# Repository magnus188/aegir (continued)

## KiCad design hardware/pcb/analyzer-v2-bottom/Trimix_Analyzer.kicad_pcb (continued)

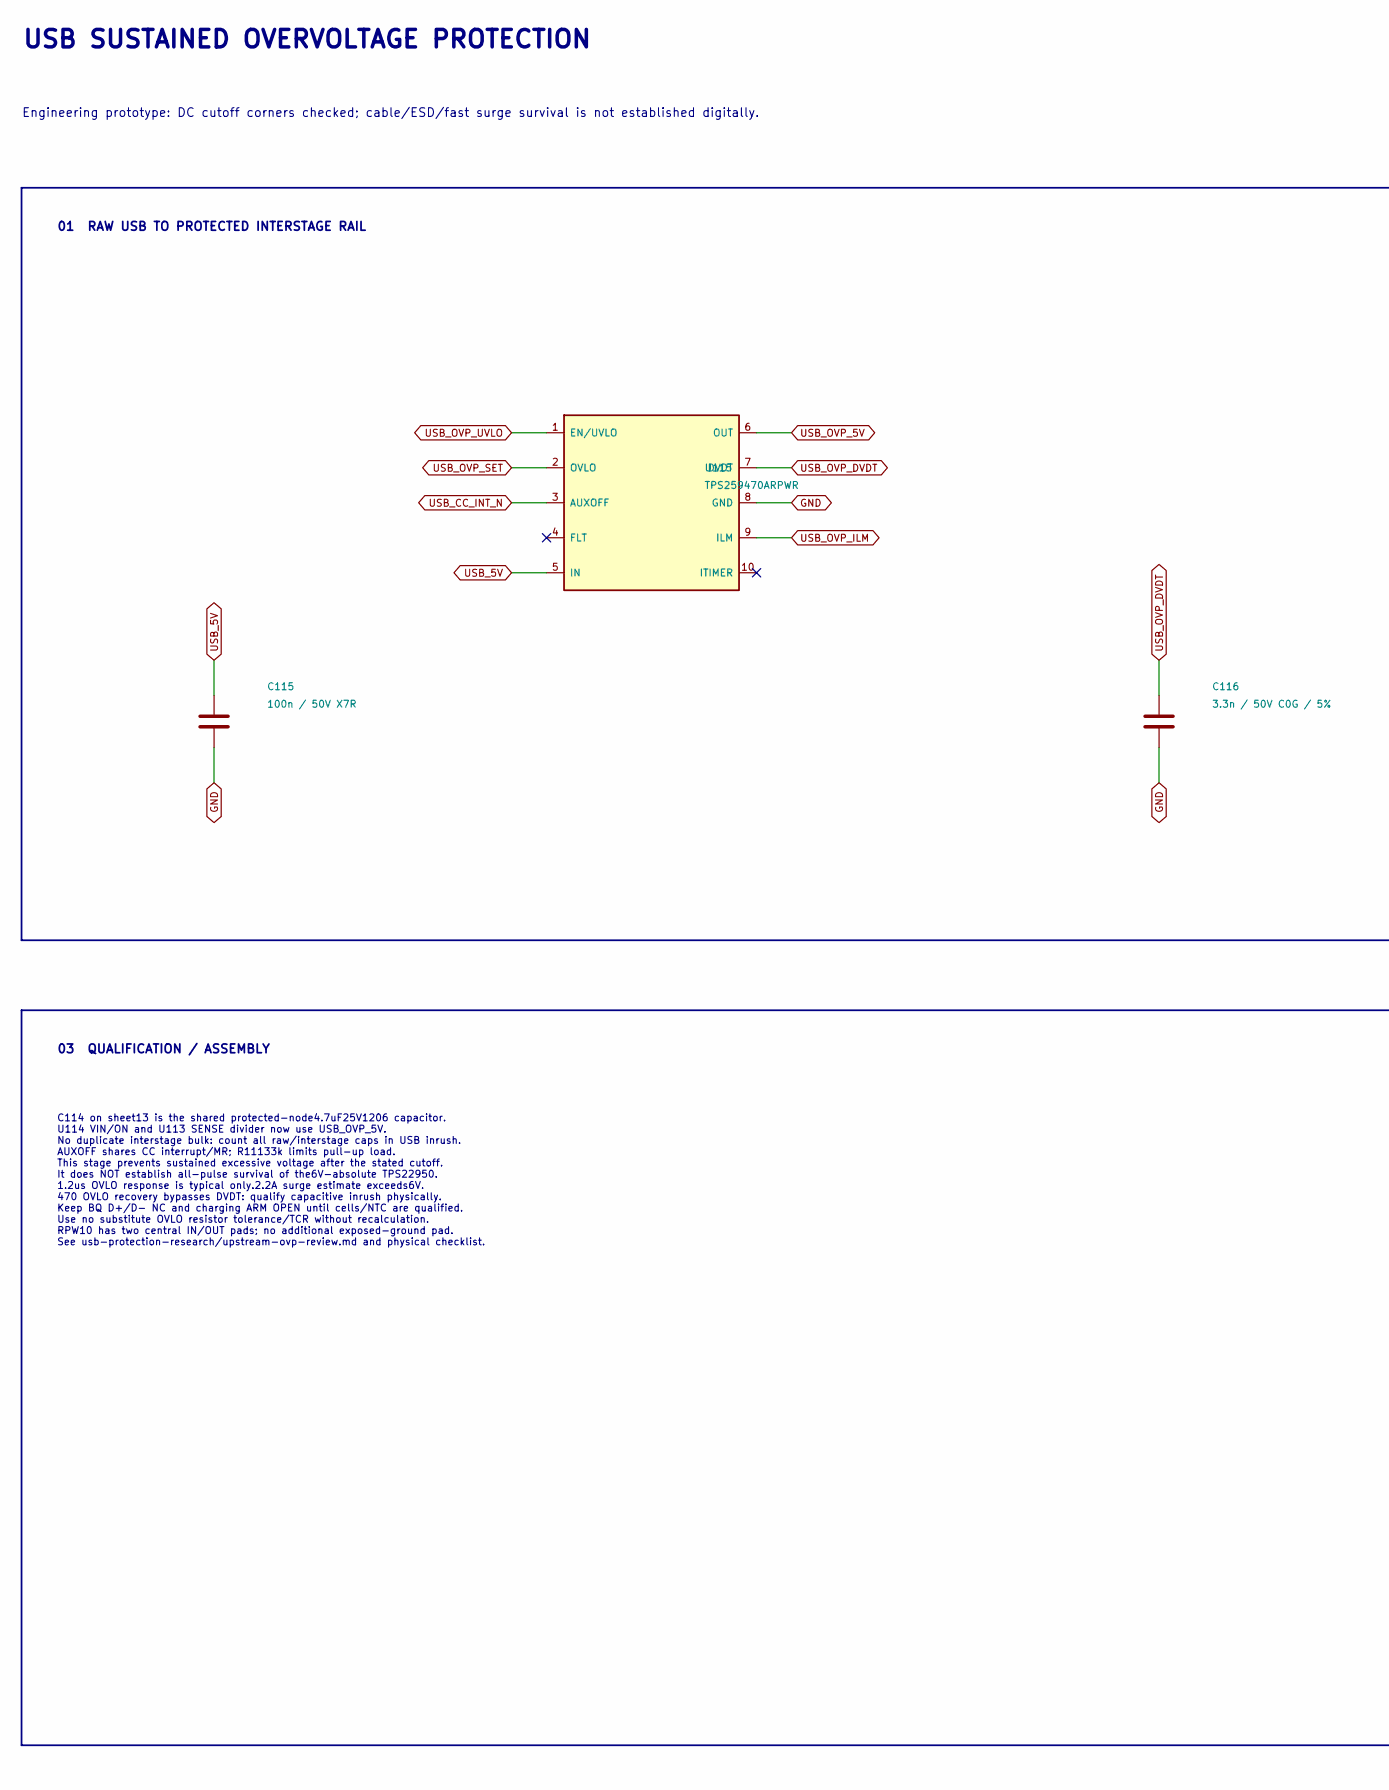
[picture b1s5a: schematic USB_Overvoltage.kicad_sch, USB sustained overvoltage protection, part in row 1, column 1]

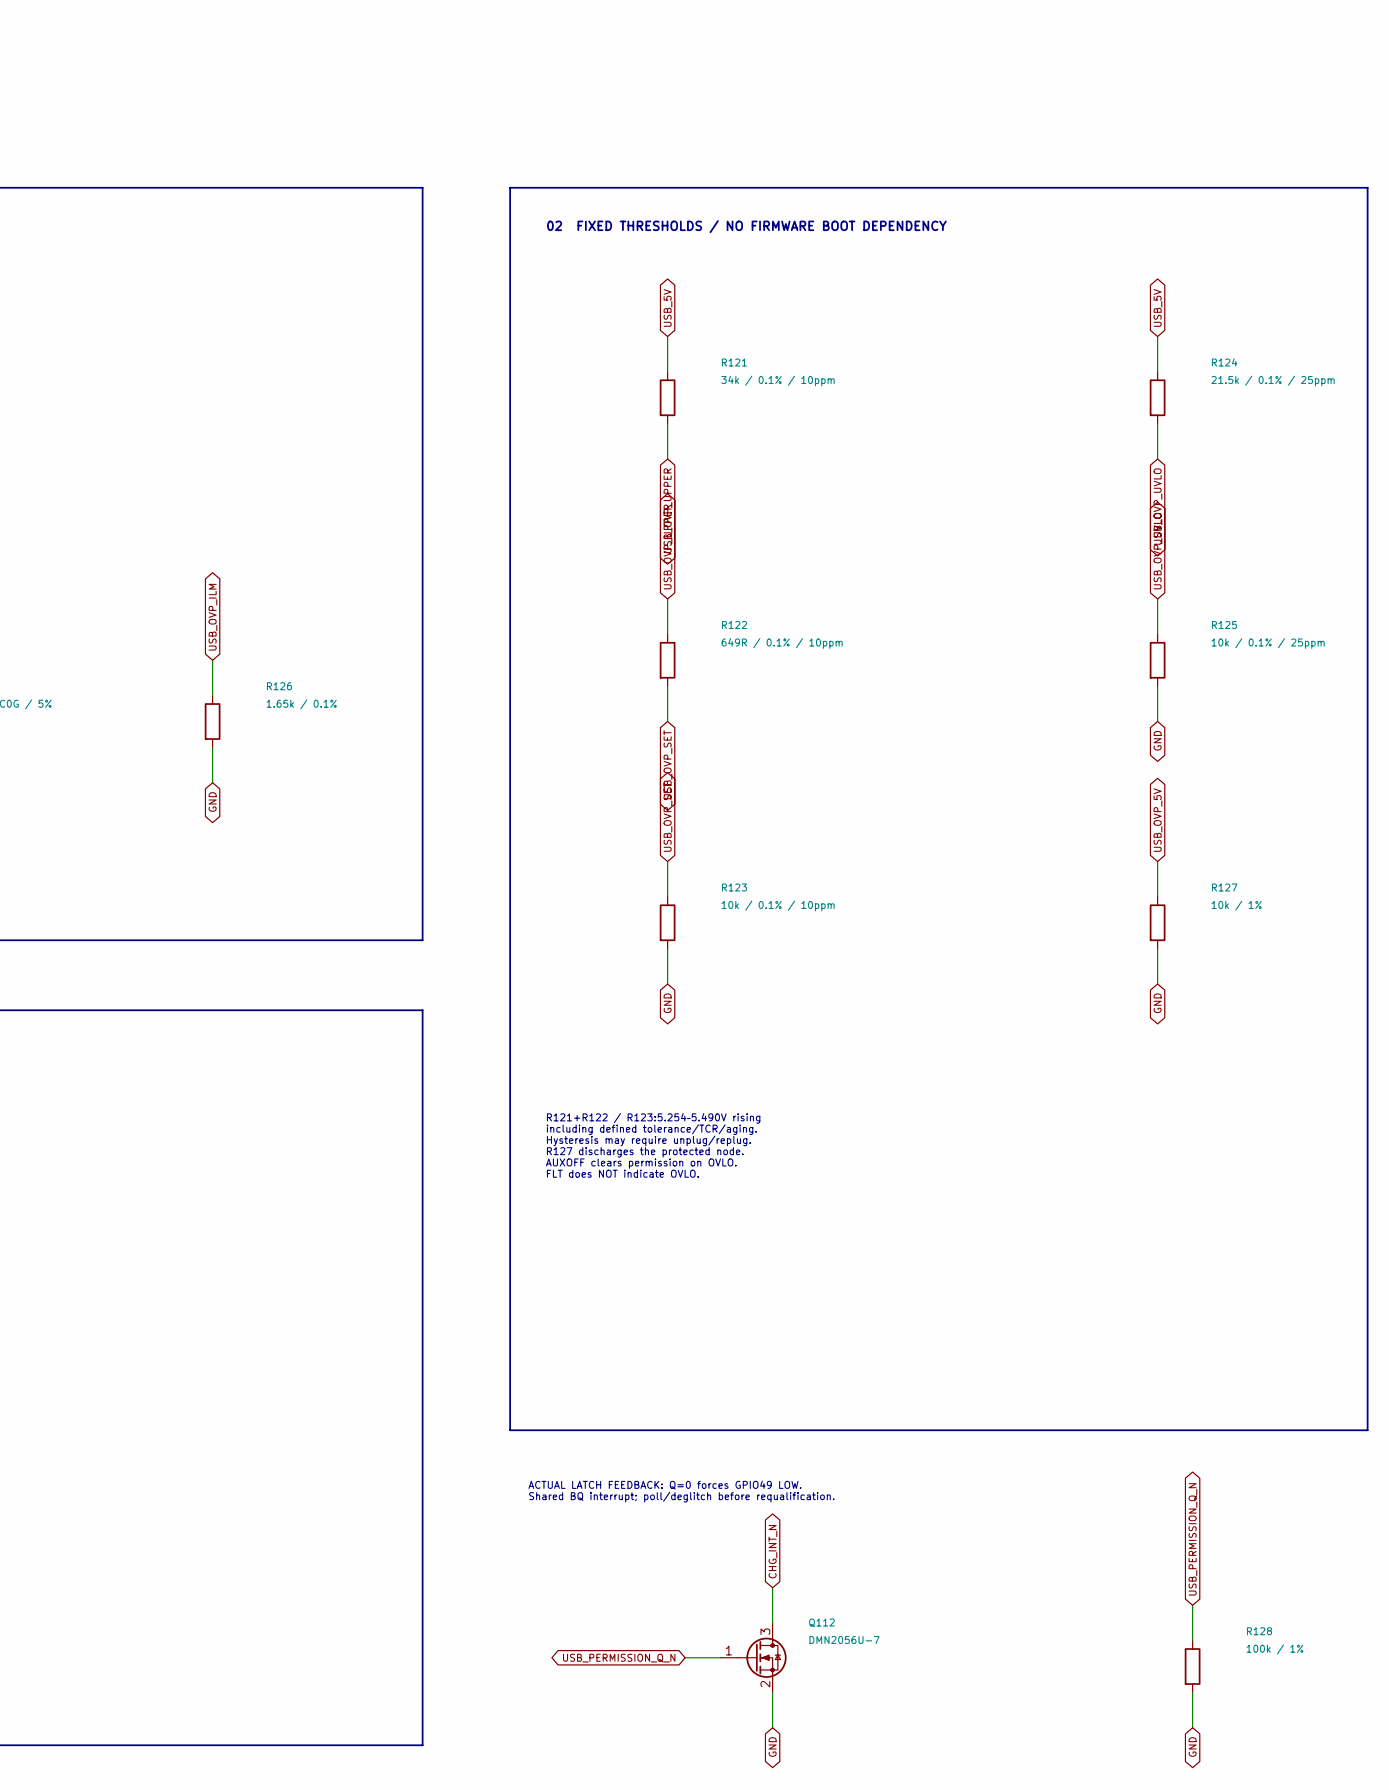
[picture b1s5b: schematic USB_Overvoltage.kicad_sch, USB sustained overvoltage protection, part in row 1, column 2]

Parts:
C115: 100n / 50V X7R; C_0603_1608Metric; MPN C1608X7R1H104K080AA
C116: 3.3n / 50V C0G / 5%; C_0402_1005Metric; MPN GRM1555C1H332JE01D
Q112: DMN2056U-7; SOT-23; MPN DMN2056U-7
R121: 34k / 0.1% / 10ppm; R_0603_1608Metric; MPN TNPW060334K0BYEA
R122: 649R / 0.1% / 10ppm; R_0603_1608Metric; MPN TNPW0603649RBYEA
R123: 10k / 0.1% / 10ppm; R_0603_1608Metric; MPN TNPW060310K0BYEA
R124: 21.5k / 0.1% / 25ppm; R_0603_1608Metric; MPN TNPW060321K5BEEA
R125: 10k / 0.1% / 25ppm; R_0603_1608Metric; MPN TNPW060310K0BEEA
R126: 1.65k / 0.1%; R_0603_1608Metric; MPN TNPW06031K65BEEA
R127: 10k / 1%; R_0603_1608Metric; MPN RC0603FR-0710KL
R128: 100k / 1%; R_0603_1608Metric; MPN RC0603FR-07100KL
U115: TPS259470ARPWR; TI_RPW0010A; MPN TPS259470ARPWR

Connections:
CHG_INT_N: Q112.3 (D); also elsewhere on the board
GND: C115.2, C116.2, Q112.2 (S), R123.2, R125.2, R126.2, R127.2, R128.2, U115.8 (GND); also elsewhere on the board
USB_5V: C115.1, R121.1, R124.1, U115.5 (IN); also elsewhere on the board
USB_CC_INT_N: U115.3 (AUXOFF); also elsewhere on the board
USB_OVP_5V: R127.1, U115.6 (OUT); also elsewhere on the board
USB_OVP_DVDT: C116.1, U115.7 (DVDT)
USB_OVP_ILM: R126.1, U115.9 (ILM)
USB_OVP_SET: R122.2, R123.1, U115.2 (OVLO)
USB_OVP_UPPER: R121.2, R122.1
USB_OVP_UVLO: R124.2, R125.1, U115.1 (EN/UVLO)
USB_PERMISSION_Q_N: Q112.1 (G), R128.1; also elsewhere on the board

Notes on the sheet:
C114 on sheet13 is the shared protected-node4.7uF25V1206 capacitor. U114 VIN/ON and U113 SENSE divider now use USB_OVP_5V. No duplicate interstage bulk: count all raw/interstage caps in USB inrush. AUXOFF shares CC interrupt/MR; R11133k limits pull-up load. This stage prevents sustained excessive v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
01 RAW USB TO PROTECTED INTERSTAGE RAIL
USB SUSTAINED OVERVOLTAGE PROTECTION
Engineering prototype: DC cutoff corners checked; cable/ESD/fast surge survival is not established digitally.
03 QUALIFICATION / ASSEMBLY
R121+R122 / R123:5.254–5.490V rising including defined tolerance/TCR/aging. Hysteresis may require unplug/replug. R127 discharges the protected node. AUXOFF clears permission on OVLO. FLT does NOT indicate OVLO.
02 FIXED THRESHOLDS / NO FIRMWARE BOOT DEPENDENCY
ACTUAL LATCH FEEDBACK: Q=0 forces GPIO49 LOW. Shared BQ interrupt; poll/deglitch before requalification.

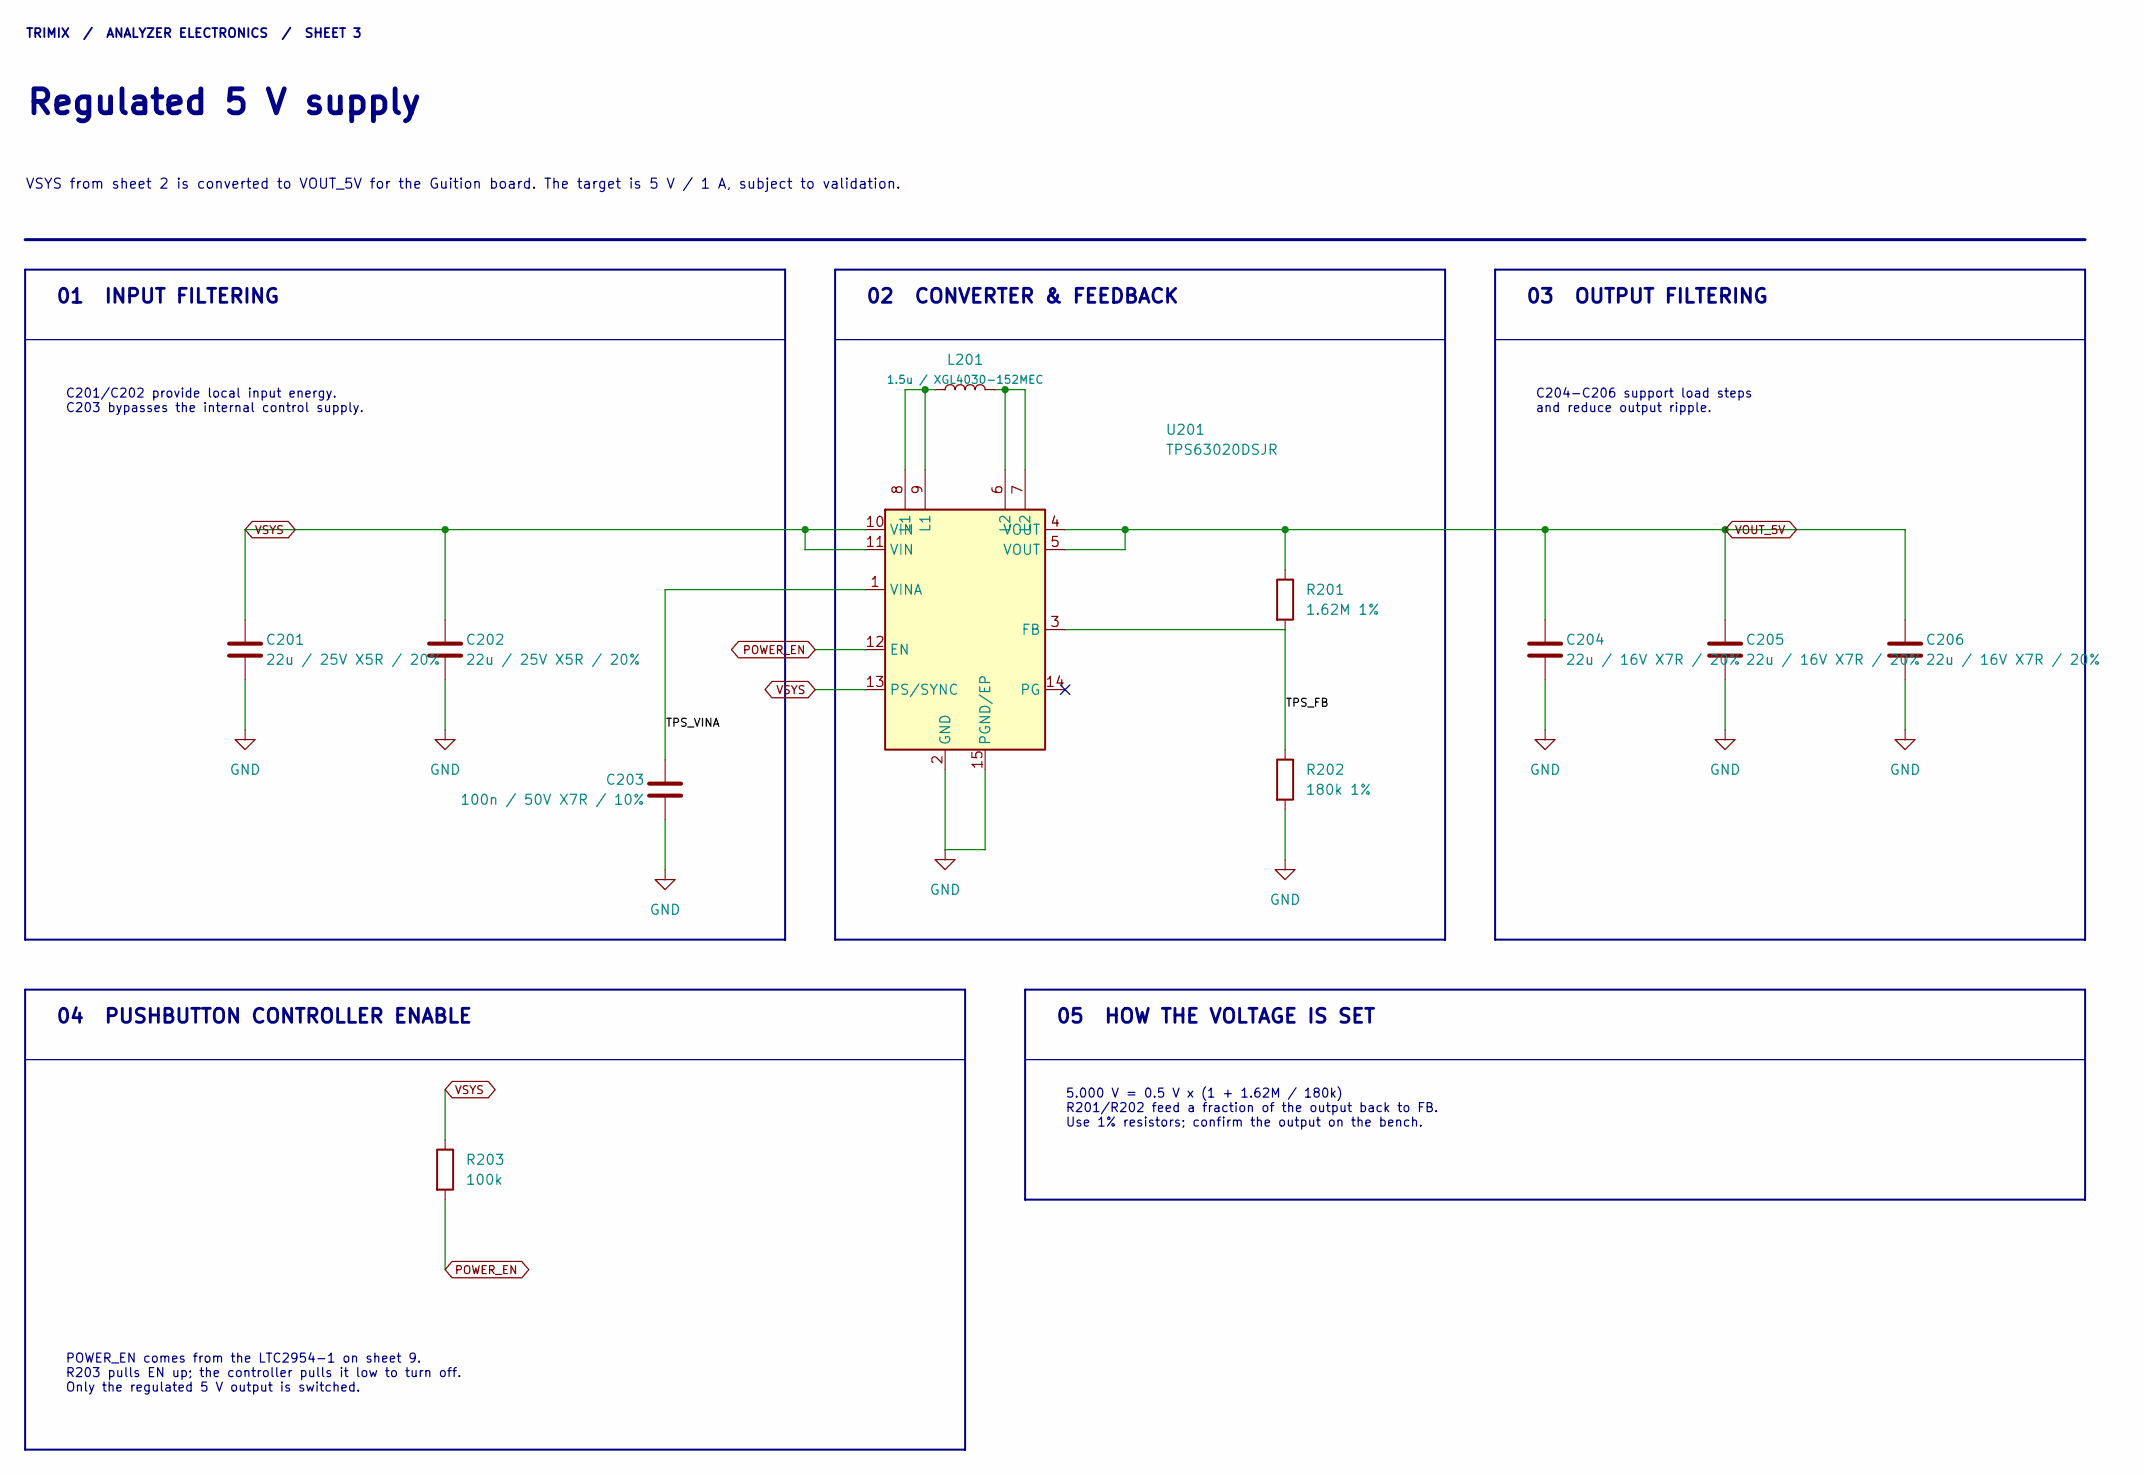
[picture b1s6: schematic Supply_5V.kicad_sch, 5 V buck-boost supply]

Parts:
C201, C202: 22u / 25V X5R / 20%; C_1206_3216Metric; MPN C3216X5R1E226M160AB
C203: 100n / 50V X7R / 10%; C_0603_1608Metric; MPN C1608X7R1H104K080AA
C204, C205, C206: 22u / 16V X7R / 20%; C_1210_3225Metric; MPN C3225X7R1C226M250AC
L201: 1.5u / XGL4030-152MEC; L_Coilcraft_XGL4030; MPN XGL4030-152MEC
R201: 1.62M 1%; R_0603_1608Metric; MPN RC0603FR-071M62L
R202: 180k 1%; R_0603_1608Metric; MPN RC0603FR-07180KL
R203: 100k; R_0603_1608Metric; MPN RC0603FR-07100KL
U201: TPS63020DSJR; TI_DSJ_14; MPN TPS63020DSJR

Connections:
/02 SWITCHED 5 V/TPS_FB: R201.2, R202.1, U201.3 (FB)
/02 SWITCHED 5 V/TPS_VINA: C203.1, U201.1 (VINA)
GND: C201.2, C202.2, C203.2, C204.2, C205.2, C206.2, R202.2, U201.2 (GND), U201.15 (PGND/EP); also elsewhere on the board
unnamed: L201.1, U201.8 (L1), U201.9 (L1)
unnamed: L201.2, U201.6 (L2), U201.7 (L2)
POWER_EN: R203.2, U201.12 (EN); also elsewhere on the board
VOUT_5V: C204.1, C205.1, C206.1, R201.1, U201.4 (VOUT), U201.5 (VOUT); also elsewhere on the board
VSYS: C201.1, C202.1, R203.1, U201.10 (VIN), U201.11 (VIN), U201.13 (PS/SYNC); also elsewhere on the board

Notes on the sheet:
02 CONVERTER & FEEDBACK
C204-C206 support load steps and reduce output ripple.
5.000 V = 0.5 V x (1 + 1.62M / 180k) R201/R202 feed a fraction of the output back to FB. Use 1% resistors; confirm the output on the bench.
VSYS from sheet 2 is converted to VOUT_5V for the Guition board. The target is 5 V / 1 A, subject to validation.
TRIMIX / ANALYZER ELECTRONICS / SHEET 3
05 HOW THE VOLTAGE IS SET
01 INPUT FILTERING
04 PUSHBUTTON CONTROLLER ENABLE
Regulated 5 V supply
C201/C202 provide local input energy. C203 bypasses the internal control supply.
03 OUTPUT FILTERING
POWER_EN comes from the LTC2954-1 on sheet 9. R203 pulls EN up; the controller pulls it low to turn off. Only the regulated 5 V output is switched.

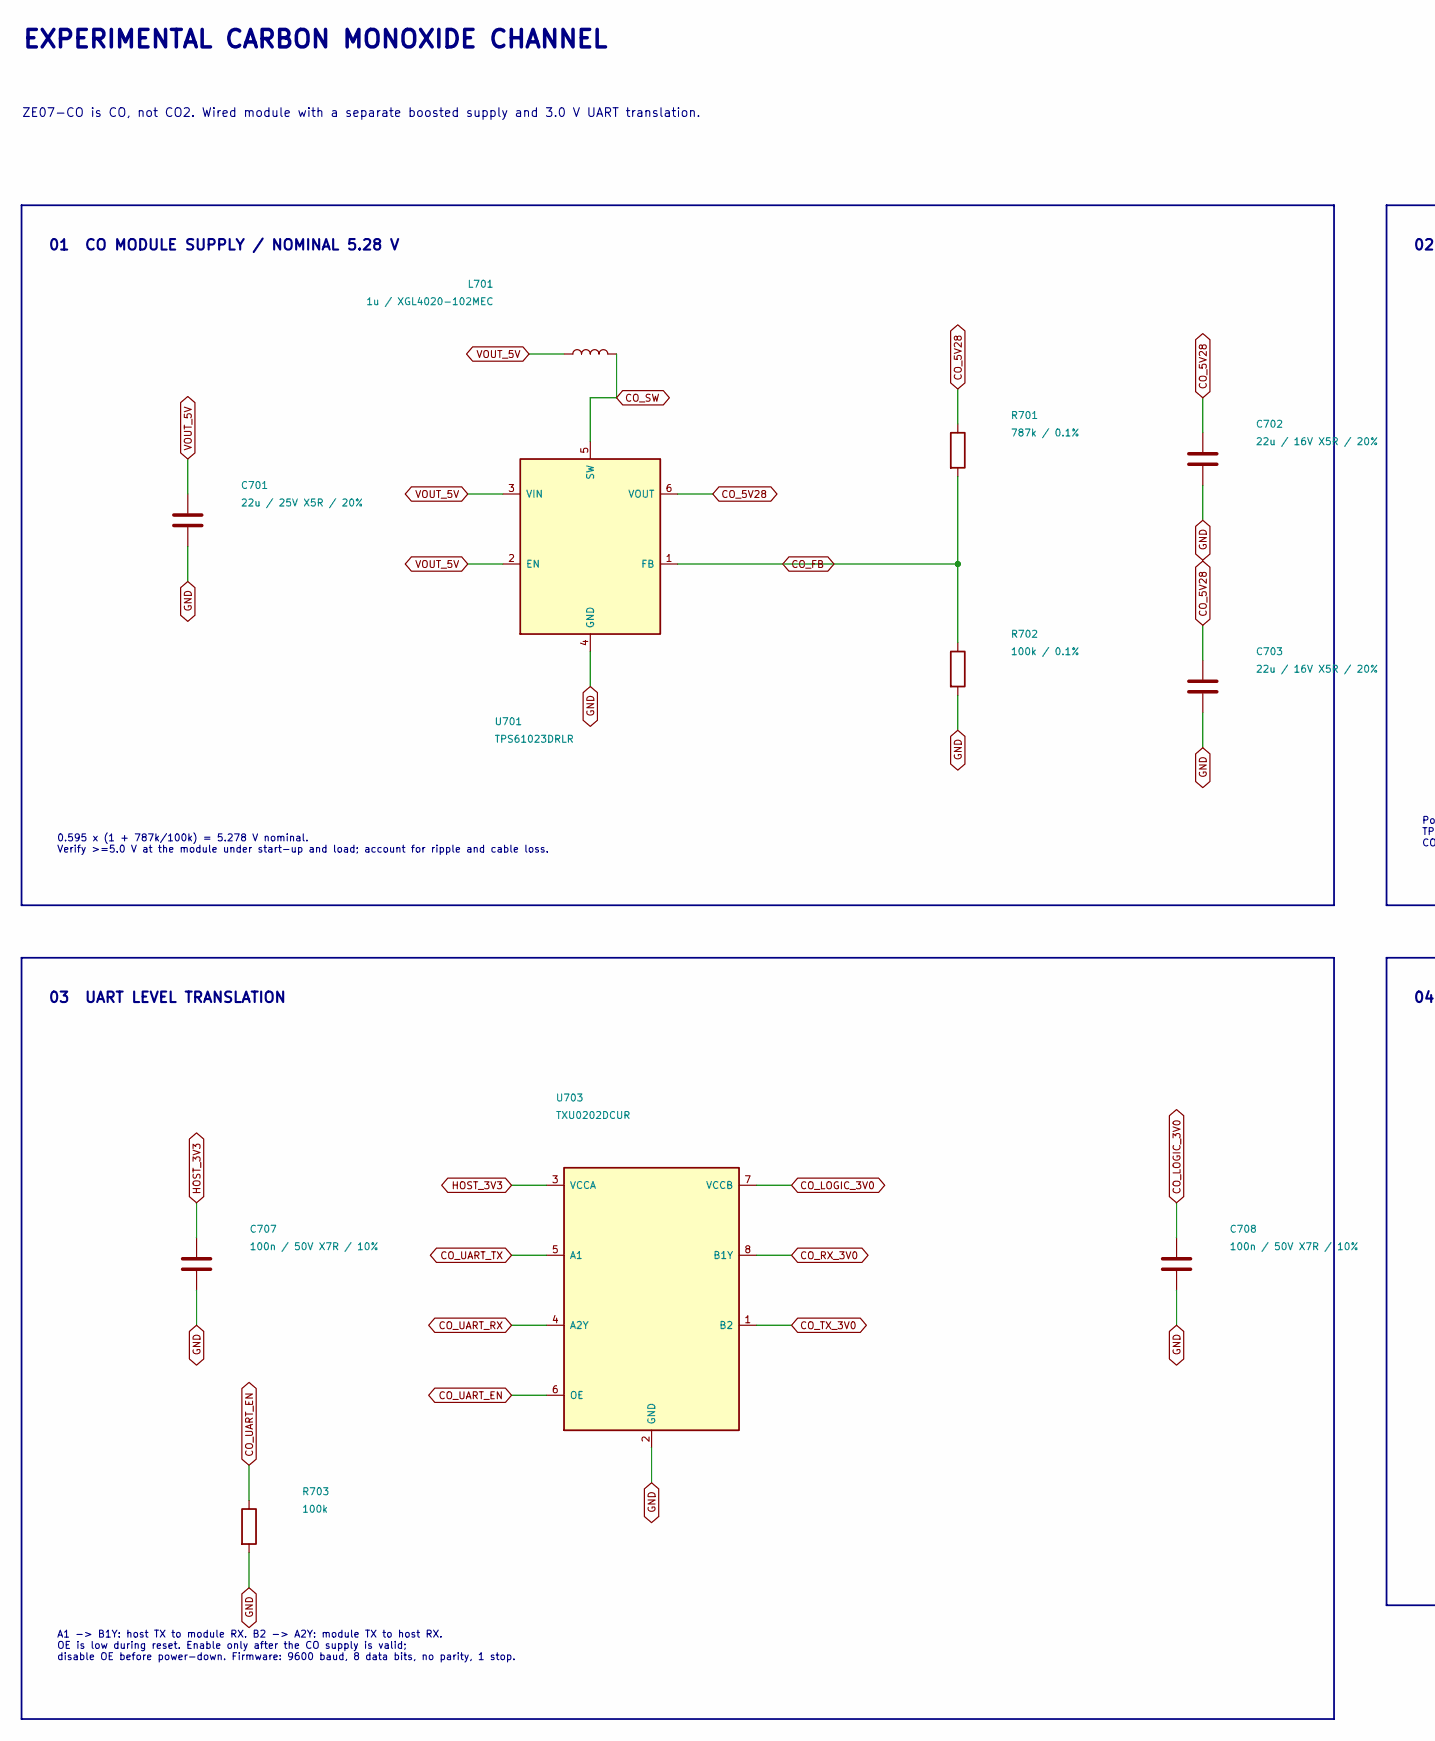
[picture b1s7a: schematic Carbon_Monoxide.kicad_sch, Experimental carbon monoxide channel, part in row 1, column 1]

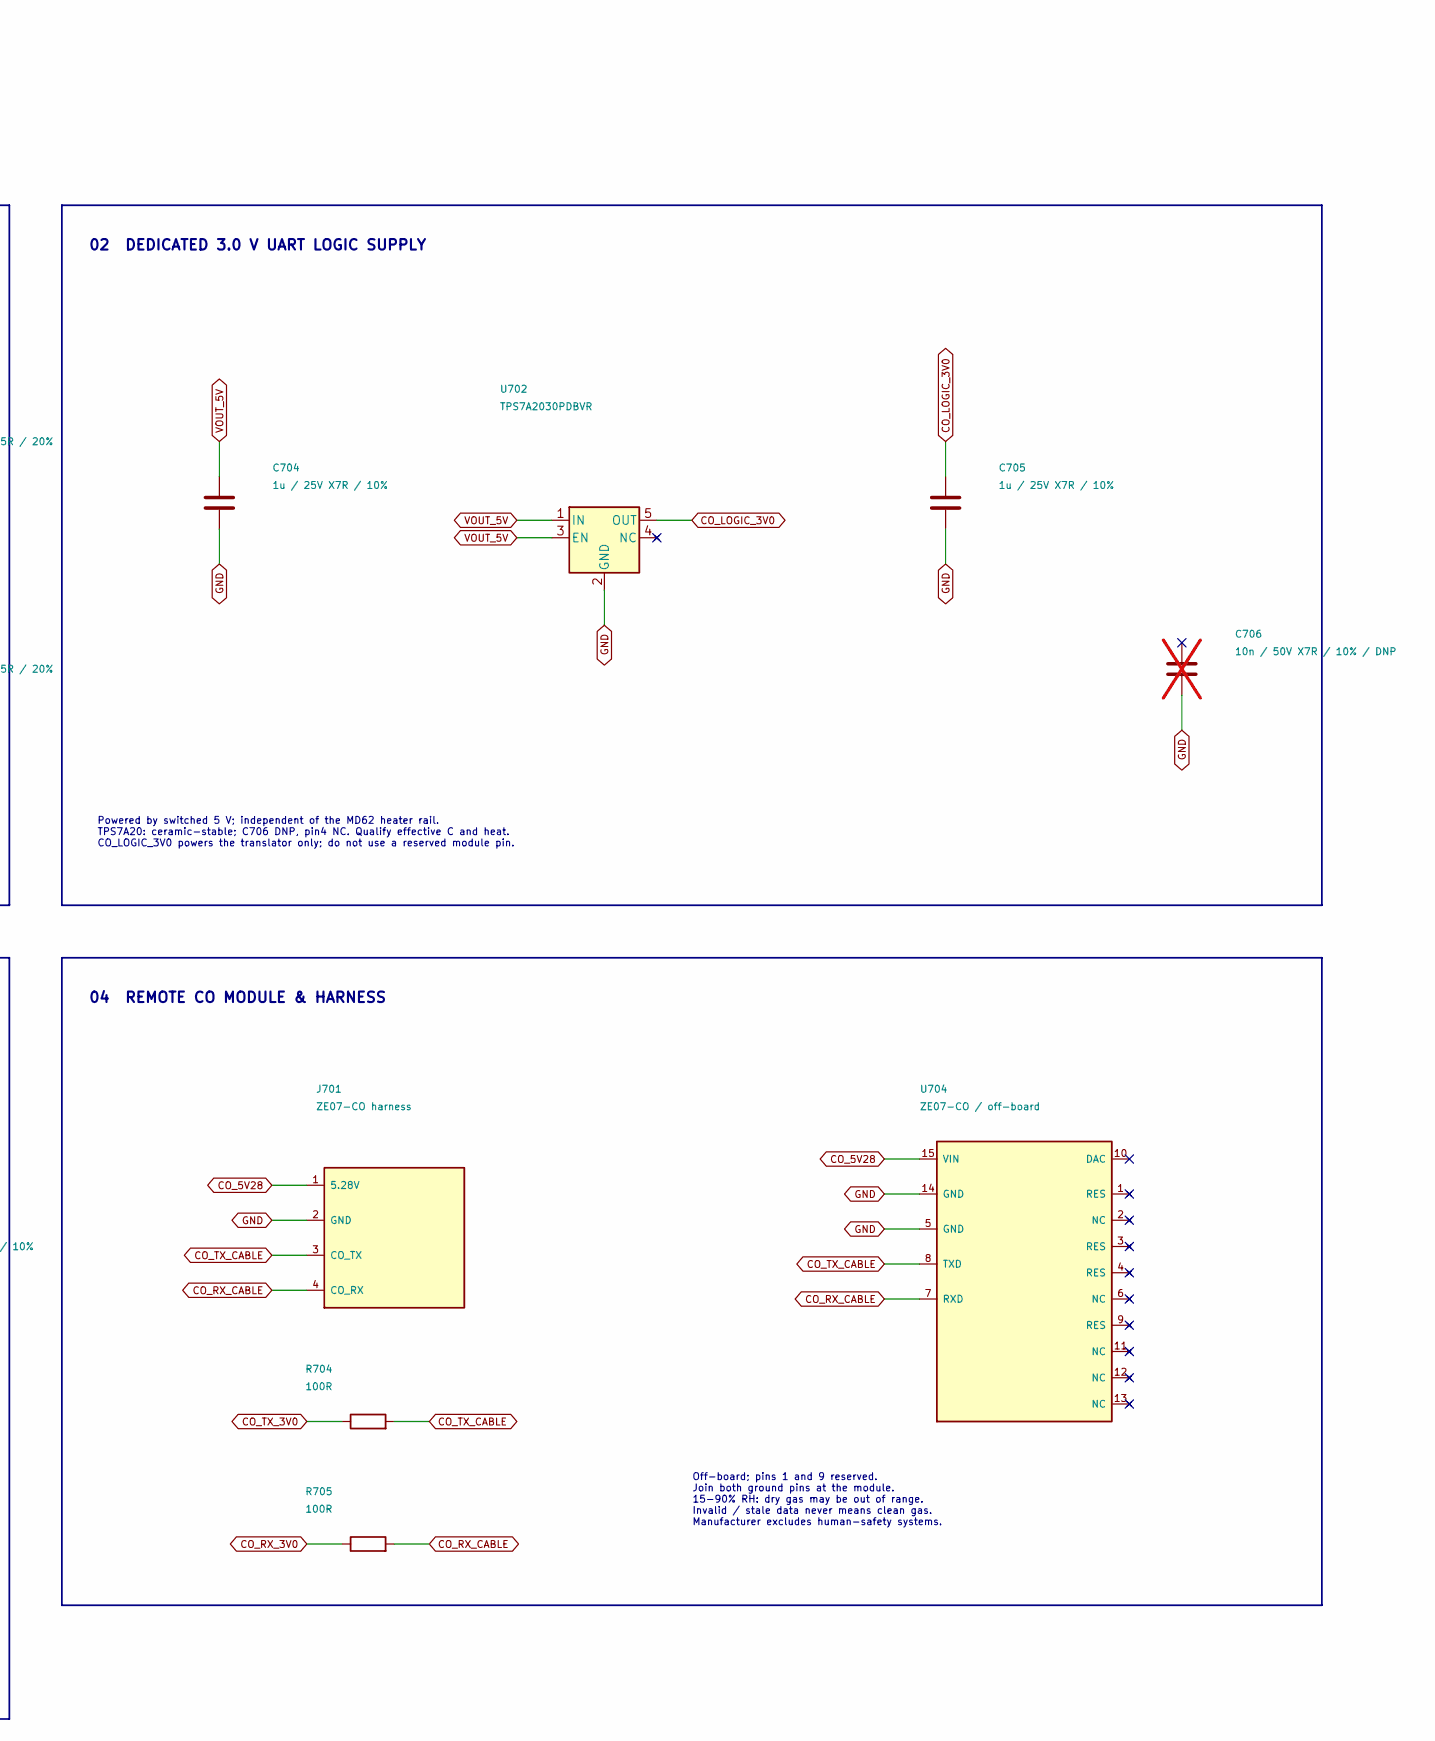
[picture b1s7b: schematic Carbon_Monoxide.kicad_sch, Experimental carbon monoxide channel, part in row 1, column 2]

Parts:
C701: 22u / 25V X5R / 20%; C_1206_3216Metric; MPN C3216X5R1E226M160AB
C702, C703: 22u / 16V X5R / 20%; C_0805_2012Metric; MPN C2012X5R1C226M125AC
C704, C705: 1u / 25V X7R / 10%; C_0805_2012Metric; MPN C2012X7R1E105K125AB
C706: 10n / 50V X7R / 10% / DNP; C_0805_2012Metric; MPN C0805C103K5RACTU; not fitted
C707, C708: 100n / 50V X7R / 10%; C_0805_2012Metric; MPN C0805C104K5RACTU
J701: ZE07-CO harness; JST_XH_B4B-XH-A_1x04_P2.50mm_Vertical; MPN B4B-XH-A(LF)(SN)
L701: 1u / XGL4020-102MEC; L_Coilcraft_XGL4020; MPN XGL4020-102MEC
R701: 787k / 0.1%; R_0603_1608Metric; MPN RT0603BRD07787KL
R702: 100k / 0.1%; R_0402_1005Metric; MPN RT0402BRD07100KL
R703: 100k; R_0603_1608Metric; MPN RC0603FR-07100KL
R704, R705: 100R; R_0603_1608Metric; MPN RC0603FR-07100RL
U701: TPS61023DRLR; SOT-563; MPN TPS61023DRLR
U702: TPS7A2030PDBVR; SOT-23-5; MPN TPS7A2030PDBVR
U703: TXU0202DCUR; TI_DCU8_CompactSilk; MPN TXU0202DCUR
U704: ZE07-CO / off-board

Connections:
CO_5V28: C702.1, C703.1, J701.1 (5.28V), R701.1, U701.6 (VOUT), U704.15 (VIN)
CO_FB: R701.2, R702.1, U701.1 (FB)
CO_LOGIC_3V0: C705.1, C708.1, U702.5 (OUT), U703.7 (VCCB)
CO_RX_3V0: R705.1, U703.8 (B1Y)
CO_RX_CABLE: J701.4 (CO_RX), R705.2, U704.7 (RXD)
CO_SW: L701.2, U701.5 (SW)
CO_TX_3V0: R704.1, U703.1 (B2)
CO_TX_CABLE: J701.3 (CO_TX), R704.2, U704.8 (TXD)
CO_UART_EN: R703.1, U703.6 (OE); also elsewhere on the board
CO_UART_RX: U703.4 (A2Y); also elsewhere on the board
CO_UART_TX: U703.5 (A1); also elsewhere on the board
GND: C701.2, C702.2, C703.2, C704.2, C705.2, C706.2, C707.2, C708.2, J701.2 (GND), R702.2, R703.2, U701.4 (GND), U702.2 (GND), U703.2 (GND), U704.5 (GND), U704.14 (GND); also elsewhere on the board
HOST_3V3: C707.1, U703.3 (VCCA); also elsewhere on the board
VOUT_5V: C701.1, C704.1, L701.1, U701.2 (EN), U701.3 (VIN), U702.1 (IN), U702.3 (EN); also elsewhere on the board

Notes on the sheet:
ZE07-CO is CO, not CO2. Wired module with a separate boosted supply and 3.0 V UART translation.
Powered by switched 5 V; independent of the MD62 heater rail. TPS7A20: ceramic-stable; C706 DNP, pin4 NC. Qualify effective C and heat. CO_LOGIC_3V0 powers the translator only; do not use a reserved module pin.
EXPERIMENTAL CARBON MONOXIDE CHANNEL
A1 -> B1Y: host TX to module RX. B2 -> A2Y: module TX to host RX. OE is low during reset. Enable only after the CO supply is valid; disable OE before power-down. Firmware: 9600 baud, 8 data bits, no parity, 1 stop.
0.595 x (1 + 787k/100k) = 5.278 V nominal. Verify >=5.0 V at the module under start-up and load; account for ripple and cable loss.
04 REMOTE CO MODULE & HARNESS
03 UART LEVEL TRANSLATION
Off-board; pins 1 and 9 reserved. Join both ground pins at the module. 15-90% RH: dry gas may be out of range. Invalid / stale data never means clean gas. Manufacturer excludes human-safety systems.
01 CO MODULE SUPPLY / NOMINAL 5.28 V
02 DEDICATED 3.0 V UART LOGIC SUPPLY
